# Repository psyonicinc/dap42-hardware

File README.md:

# dap42-hardware

This is a design of the dap42 in KiCad v6 using the STM32F103C8, there is no technical reason for this design and this STM is overkill. The re-design only part availability reasons. This design is based on dap42 v2 and [dc37's dap42 v3 design](https://github.com/dc37/dap42-hardware). 

Please see the parent repo at [devanlai/dap42-hardware](https://github.com/devanlai/dap42-hardware) for details on the DAP42 project. 

This design primarily uses the [KiCad default libraries](https://gitlab.com/kicad/libraries) which are expected to be in the global library table. A few footprints not in the KiCad Libraries are included in dap42.pretty which is configured as a project specific library. 

Firmware for this version to follow.

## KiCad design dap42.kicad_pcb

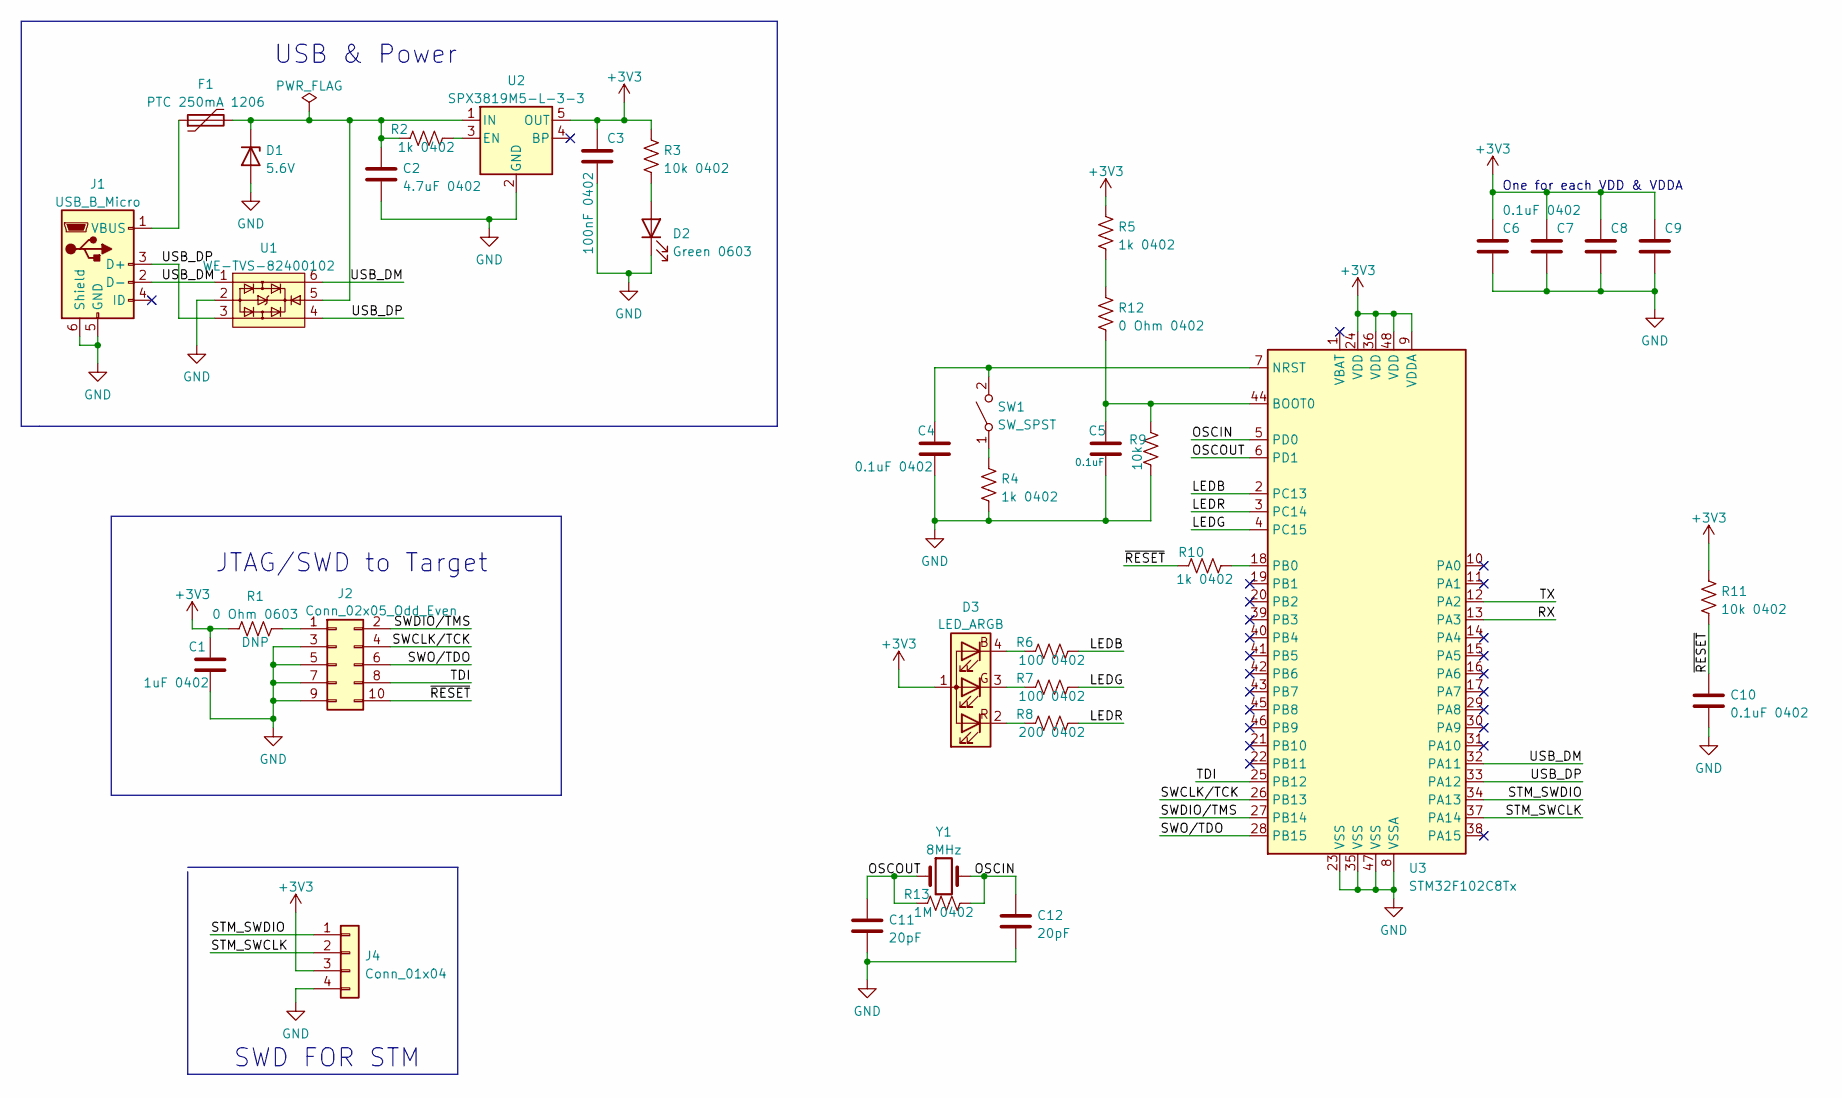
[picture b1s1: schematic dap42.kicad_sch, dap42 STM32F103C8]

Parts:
C1: 1uF 0402; C_0402_1005Metric_Pad0.74x0.62mm_HandSolder
C2: 4.7uF 0402; C_0402_1005Metric_Pad0.74x0.62mm_HandSolder
C3: 100nF 0402; C_0402_1005Metric_Pad0.74x0.62mm_HandSolder
C4, C6, C7, C8, C9, C10: 0.1uF 0402; C_0402_1005Metric_Pad0.74x0.62mm_HandSolder
C5: 0.1uF; C_0402_1005Metric_Pad0.74x0.62mm_HandSolder
C11, C12: 20pF; C_0402_1005Metric_Pad0.74x0.62mm_HandSolder
D1: 5.6V; D_SOD-123F; MPN NZH5V6B
D2: Green 0603; LED_0603_1608Metric_Pad1.05x0.95mm_HandSolder
D3: LED_ARGB; XZCMEDGCBD110W; MPN XZCMEDGCBD110W
F1: PTC 250mA 1206; Fuse_1206_3216Metric_Pad1.42x1.75mm_HandSolder
J1: USB_B_Micro; USB_Micro-B_Molex_47346-0001
J2: Conn_02x05_Odd_Even; IDC-Header_2x05_Pitch1.27mm_Straight
J4: Conn_01x04; PinHeader_1x04_P2.54mm_Vertical
R1: 0 Ohm 0603; R_0603_1608Metric_Pad0.98x0.95mm_HandSolder
R2, R4, R5, R10: 1k 0402; R_0402_1005Metric_Pad0.72x0.64mm_HandSolder
R3, R11: 10k 0402; R_0402_1005Metric_Pad0.72x0.64mm_HandSolder
R6, R7: 100 0402; R_0402_1005Metric_Pad0.72x0.64mm_HandSolder
R8: 200 0402; R_0402_1005Metric_Pad0.72x0.64mm_HandSolder
R9: 10k; R_0402_1005Metric_Pad0.72x0.64mm_HandSolder
R12: 0 Ohm 0402; R_0402_1005Metric_Pad0.72x0.64mm_HandSolder
R13: 1M 0402; R_0402_1005Metric_Pad0.72x0.64mm_HandSolder
SW1: SW_SPST; SW_Push_1P1T_NO_CK_KMR2
U1: WE-TVS-82400102; SOT-23-6
U2: SPX3819M5-L-3-3; SOT-23-5
U3: STM32F102C8Tx; LQFP-48_7x7mm_P0.5mm
Y1: 8MHz; Crystal_HC49-U_Vertical; MPN 8M20P2/49US

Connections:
+3V3: C1.1, C3.1, C6.1, C7.1, C8.1, C9.1, D3.1 (A), J4.3, R1.1, R3.1, R5.1, R11.1, U2.5 (OUT), U3.9 (VDDA), U3.24 (VDD), U3.36 (VDD), U3.48 (VDD)
/LEDB: R6.1, U3.2 (PC13)
/LEDG: R7.1, U3.4 (PC15)
/LEDR: R8.1, U3.3 (PC14)
/OSCIN: C12.1, R13.1, U3.5 (PD0), Y1.2
/OSCOUT: C11.1, R13.2, U3.6 (PD1), Y1.1
/RX: U3.13 (PA3)
/STM_SWCLK: J4.2, U3.37 (PA14)
/STM_SWDIO: J4.1, U3.34 (PA13)
/SWCLK/TCK: J2.4, U3.26 (PB13)
/SWDIO/TMS: J2.2, U3.27 (PB14)
/SWO/TDO: J2.6, U3.28 (PB15)
/TDI: J2.8, U3.25 (PB12)
/TX: U3.12 (PA2)
/USB_DM: J1.2 (D-), U1.1, U1.6, U3.32 (PA11)
/USB_DP: J1.3 (D+), U1.3, U1.4, U3.33 (PA12)
/~RESET: C10.1, J2.10, R10.1, R11.2
GND: C1.2, C2.2, C3.2, C4.2, C5.2, C6.2, C7.2, C8.2, C9.2, C10.2, C11.2, C12.2, D1.2 (A), D2.1 (K), J1.5 (GND), J1.6 (Shield), J2.3, J2.5, J2.7, J2.9, J4.4, R4.2, R9.2, U1.2, U2.2 (GND), U3.8 (VSSA), U3.23 (VSS), U3.35 (VSS), U3.47 (VSS)
unnamed: C2.1, D1.1 (K), F1.2, R2.1, U1.5, U2.1 (IN)
unnamed: C4.1, SW1.2 (B), U3.7 (NRST)
unnamed: C5.1, R9.1, R12.2, U3.44 (BOOT0)
unnamed: D2.2 (A), R3.2
unnamed: D3.2 (RK), R8.2
unnamed: D3.3 (GK), R7.2
unnamed: D3.4 (BK), R6.2
unnamed: F1.1, J1.1 (VBUS)
unnamed: J2.1, R1.2
unnamed: R2.2, U2.3 (EN)
unnamed: R4.1, SW1.1 (A)
unnamed: R10.2, U3.18 (PB0)
unnamed: R5.2, R12.1

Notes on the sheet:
SWD FOR STM
USB & Power
One for each VDD & VDDA
JTAG/SWD to Target

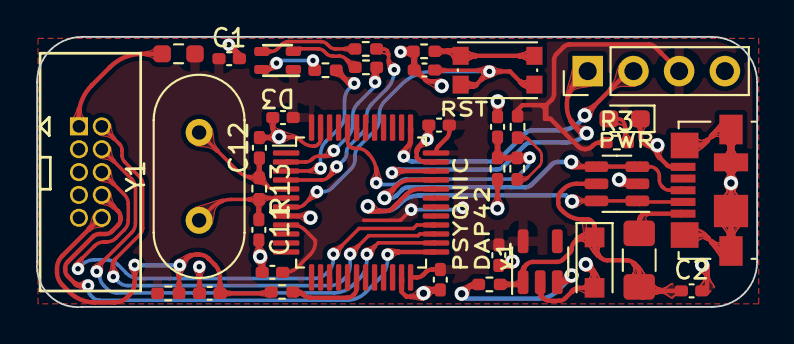
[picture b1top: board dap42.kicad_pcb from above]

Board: 2 copper layers, 40.0 x 15.0 mm, 37 parts (0 on the bottom side), 29 nets.

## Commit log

2022-05-16 KiCad DAP42 STMF103C8
2022-05-16 Readme updates
2022-05-16 Fab files
2022-05-17 Add dimensions, add pdf of schematic
2022-05-18 Note on Libraries in Readme
2022-06-03 Add BOM and Pick/Place CSV
2022-07-12 Add crystal
